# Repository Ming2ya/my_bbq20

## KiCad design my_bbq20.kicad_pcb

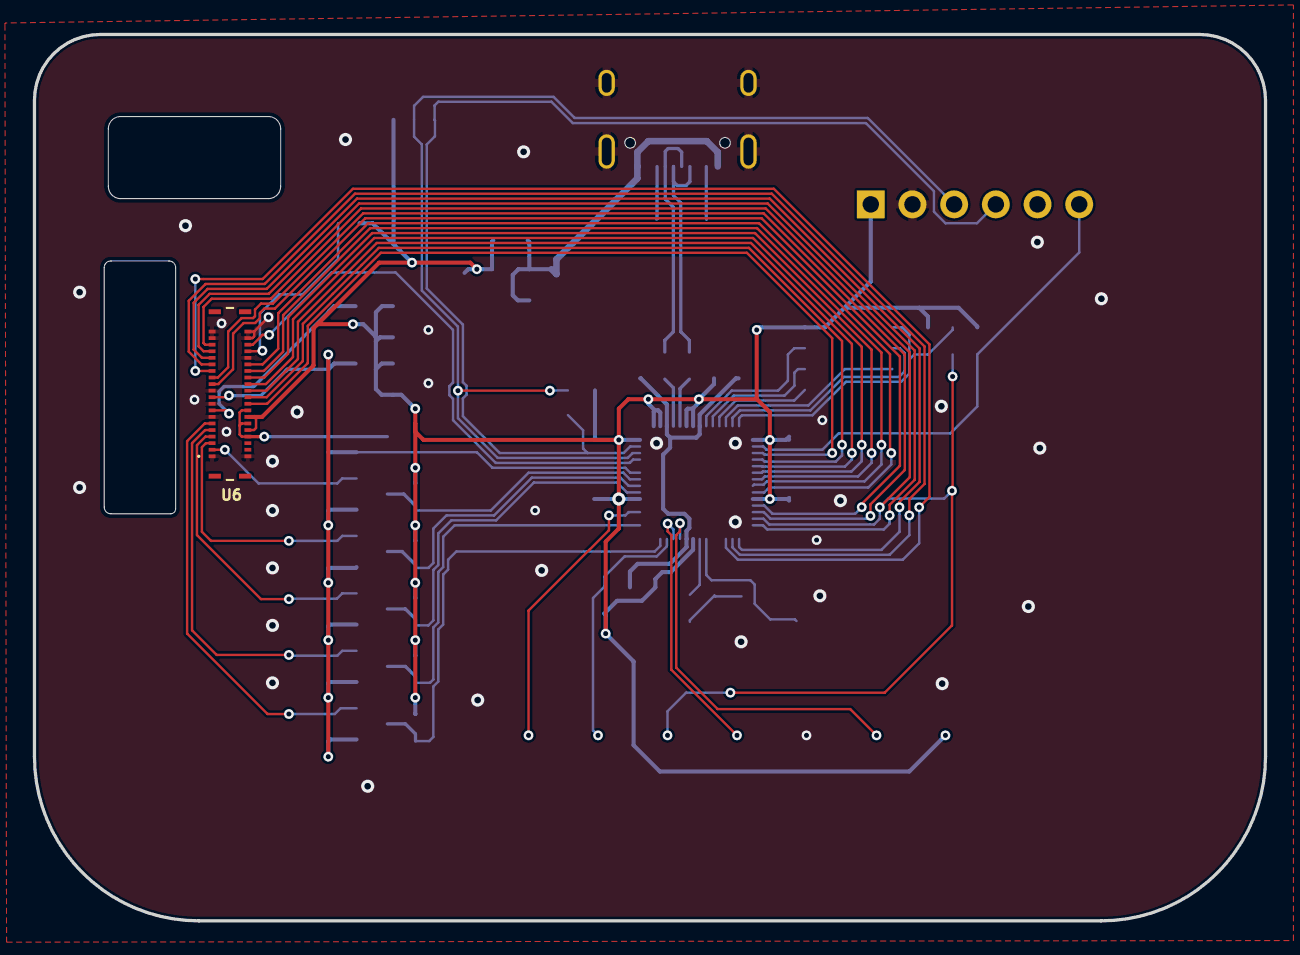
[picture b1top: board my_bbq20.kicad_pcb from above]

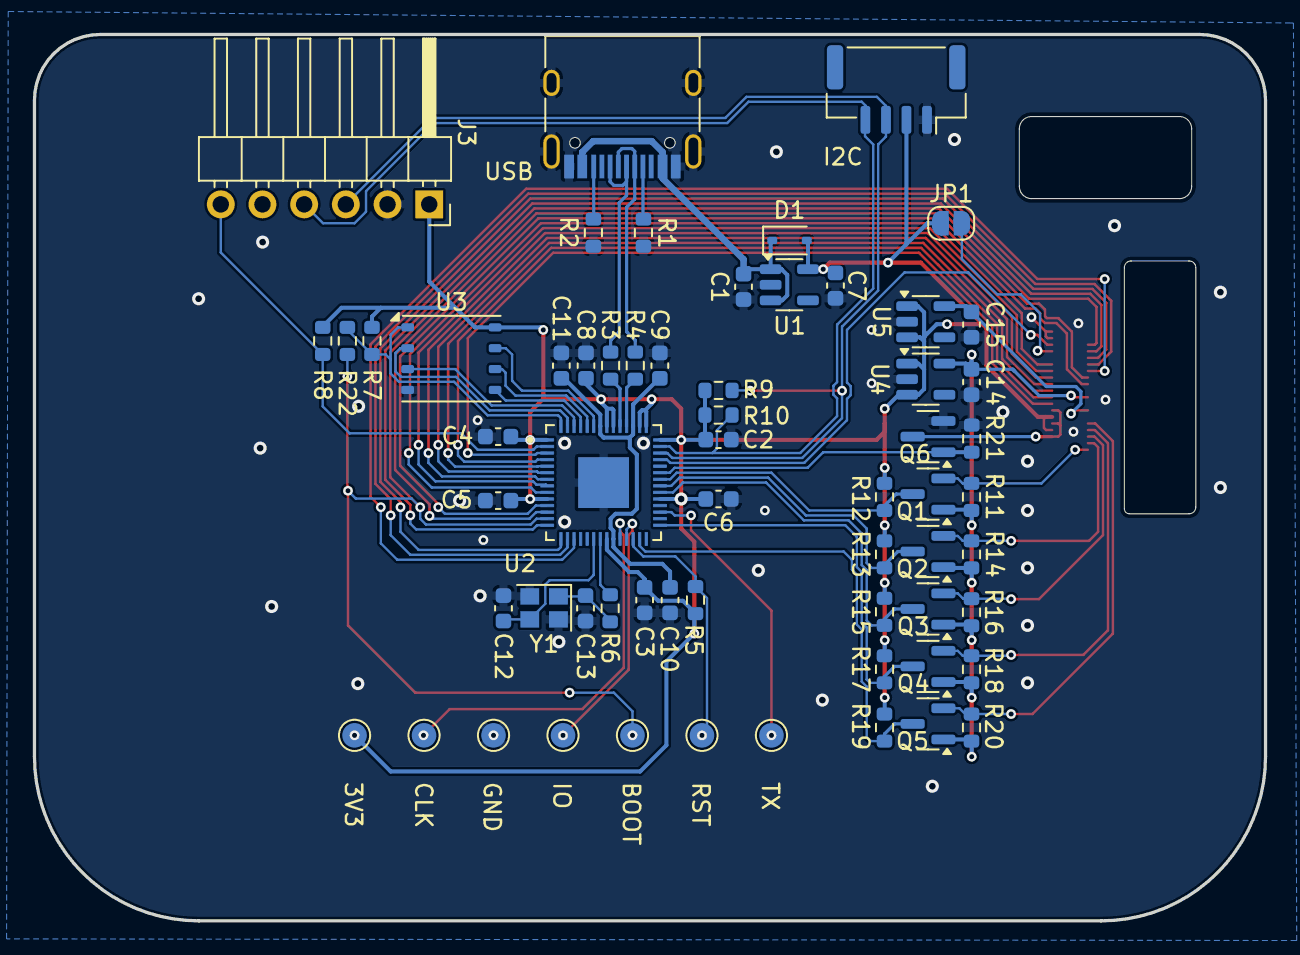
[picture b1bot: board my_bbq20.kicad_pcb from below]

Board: 2 copper layers, 75.0 x 54.0 mm, 62 parts (61 on the bottom side), 56 nets.

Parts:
3V3: TestPoint; TestPoint_Pad_D1.5mm
BOOT: TestPoint; TestPoint_Pad_D1.5mm
C1, C2: 10uF; C_0603_1608Metric
C3, C4, C5, C6, C7, C9, C10, C14, C15: 0.1uF; C_0603_1608Metric
C8, C11: 1uF; C_0603_1608Metric
C12, C13: 12pF; C_0603_1608Metric
CLK: TestPoint; TestPoint_Pad_D1.5mm
D1: D_Schottky_Small; D_SOD-323
GND: TestPoint; TestPoint_Pad_D1.5mm
I2C: Conn_01x04; JST_GH_SM04B-GHS-TB_1x04-1MP_P1.25mm_Horizontal
IO: TestPoint; TestPoint_Pad_D1.5mm
J3: PMOD; Pmod_PinHeader_1x06_P2.54mm_Horizontal
JP1: SolderJumper_2_Open; SolderJumper-2_P1.3mm_Open_RoundedPad1.0x1.5mm
Q1, Q2, Q3, Q4, Q5, Q6: BSS138; SOT-23
R1, R2: 5.1k; R_0603_1608Metric
R3, R4: 27R; R_0603_1608Metric
R5, R7, R11, R12, R13, R14, R15, R16, R17, R18, R19, R20, R21: 10k; R_0603_1608Metric
R6, R22: 1k; R_0603_1608Metric
R8, R9, R10: 4.7k; R_0603_1608Metric
RST: TestPoint; TestPoint_Pad_D1.5mm
TX: TestPoint; TestPoint_Pad_D1.5mm
U1: AP2112K-3.3; SOT-23-5
U2: QFN40P700X700X90-57N
U3: W25Q64JV; my_WSON-8-1EP_6x5mm_P1.27mm_EP3.4x4mm
U4: ME6212C18M5G; SOT-23-5
U5: ME6212C28M5G; SOT-23-5
U6: BBQ20KBD; HRS_BM20B_0.8_-40DS-0.4V_51_
USB: USB_C_Receptacle_USB2.0_16P; USB_C_Receptacle_HRO_TYPE-C-31-M-12
Y1: Crystal_GND24_Small; Crystal_SMD_2520-4Pin_2.5x2.0mm

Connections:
+1V8: C14.1, Q1.1 (G), Q2.1 (G), Q3.1 (G), Q4.1 (G), Q5.1 (G), R11.1, R14.1, R16.1, R18.1, R20.1, U4.5 (OUT), U6.10 (1V8)
+2V8: C15.1, U5.5 (OUT), U6.8 (2V8)
+3V3: 3V3.1, C2.1, C3.2, C4.2, C5.2, C6.2, C7.2, C8.2, D1.2 (A), I2C.2, J3.1, JP1.1 (A), R5.1, R7.1, R8.1, R9.1, R10.1, R12.1, R13.1, R15.1, R17.1, R19.1, U1.5 (VOUT), U2.1 (IOVDD), U2.10 (IOVDD), U2.22 (IOVDD), U2.33 (IOVDD), U2.42 (IOVDD), U2.43 (ADC_AVDD), U2.44 (VREG_IN), U2.48 (USB_VDD), U2.49 (IOVDD), U3.8 (VDD), U4.1 (IN), U4.3 (EN), U5.1 (IN), U5.3 (EN), U6.34 (LEDA), U6.36 (LEDA)
+5V: C1.1, D1.1 (K), U1.1 (VIN), U1.3 (EN), USB.A4 (VBUS), USB.A9 (VBUS), USB.B4 (VBUS), USB.B9 (VBUS)
/BACKLIGHT: Q6.1 (G), R21.1, U2.37 (GPIO25)
/BOOTSEL: BOOT.1, R22.1, U2.13 (GPIO10), U6.18 (COL7)
/COL1: U2.11 (GPIO8), U6.12 (COL1)
/COL2: U2.12 (GPIO9), U6.13 (COL2)
/COL3: U2.17 (GPIO14), U6.14 (COL3)
/COL4: U2.16 (GPIO13), U6.15 (COL4)
/COL5: U2.15 (GPIO12), U6.16 (COL5)
/COL6: U2.14 (GPIO11), U6.17 (COL6)
/INT: J3.6, R8.2, U2.2 (GPIO0)
/Keyborad/TP_MOTION_1V8: Q3.2 (S), R16.2, U6.4 (TP_MOTION)
/Keyborad/TP_RESET_1V8: Q5.2 (S), R20.2, U6.6 (TP_RESET)
/Keyborad/TP_SCL_1V8: Q2.2 (S), R14.2, U6.3 (TP_SCL)
/Keyborad/TP_SDA_1V8: Q4.2 (S), R18.2, U6.5 (TP_SDA)
/Keyborad/TP_SHUTDOWN_1V8: Q1.2 (S), R11.2, U6.2 (TP_SHUTDOWN)
/MIC: U2.39 (GPIO27_ADC1), U6.23 (MIC)
/QSPI_SCLK: U2.52 (QSPI_SCLK), U3.6 (SCK)
/QSPI_SD0: U2.53 (QSPI_SD0), U3.5 (DI/IO0)
/QSPI_SD1: U2.55 (QSPI_SD1), U3.2 (DO/IO1)
/QSPI_SD2: U2.54 (QSPI_SD2), U3.3 (~WP/IO2)
/QSPI_SD3: U2.51 (QSPI_SD3), U3.7 (~HOLD/IO3)
/ROW1: U2.3 (GPIO1), U6.32 (ROW1)
/ROW2: U2.4 (GPIO2), U6.31 (ROW2)
/ROW3: U2.5 (GPIO3), U6.30 (ROW3)
/ROW4: U2.6 (GPIO4), U6.29 (ROW4)
/ROW5: U2.7 (GPIO5), U6.28 (ROW5)
/ROW6: U2.8 (GPIO6), U6.27 (ROW6)
/ROW7: U2.9 (GPIO7), U6.26 (ROW7)
/SCL: I2C.4, J3.4, R10.2, U2.41 (GPIO29_ADC3)
/SDA: I2C.3, J3.3, R9.2, U2.40 (GPIO28_ADC2)
/SWCLK: CLK.1, U2.24 (SWCLK)
/SWDIO: IO.1, U2.25 (SWD)
/TP_MOTION: Q3.3 (D), R15.2, U2.34 (GPIO22)
/TP_RESET: Q5.3 (D), R19.2, U2.27 (GPIO16)
/TP_SCL: Q2.3 (D), R13.2, U2.35 (GPIO23)
/TP_SDA: Q4.3 (D), R17.2, U2.29 (GPIO18)
/TP_SHUTDOWN: Q1.3 (D), R12.2, U2.36 (GPIO24)
/TX: TX.1, U2.31 (GPIO20)
/USB_D+: R3.1, USB.A6 (D+), USB.B6 (D+)
/USB_D-: R4.1, USB.A7 (D-), USB.B7 (D-)
/~QSPI_CS: R7.2, R22.2, U2.56 (QSPI_SS), U3.1 (~CS)
/~RESET: R5.2, RST.1, U2.26 (RUN)
GND: C1.2, C2.2, C3.1, C4.1, C5.1, C6.1, C7.1, C8.1, C9.2, C10.2, C11.2, C12.1, C13.1, C14.2, C15.2, GND.1, I2C.1, J3.2, Q6.2 (S), R1.2, R2.2, R21.2, U1.2 (GND), U2.57 (GND), U3.4 (GND), U4.2 (GND), U5.2 (GND), U6.1 (GND), U6.7 (GND), U6.9 (GND), U6.11 (GND), U6.19 (GND), U6.20 (GND), U6.21 (GND), U6.22 (AGND), U6.25 (GND), U6.40 (GND), USB.A1 (GND), USB.A12 (GND), USB.B1 (GND), USB.B12 (GND), USB.S1 (SHIELD), Y1.2, Y1.4
unnamed: C13.2, R6.1, Y1.1
unnamed: R1.1, USB.A5 (CC1)
unnamed: R2.1, USB.B5 (CC2)
unnamed: JP1.2 (B), U6.24 (MIC_VDD)
unnamed: Q6.3 (D), U6.33 (LEDK), U6.35 (LEDK), U6.37 (LEDK)
unnamed: R3.2, U2.47 (USB_D+)
unnamed: R4.2, U2.46 (USB_D-)
unnamed: C9.1, C10.1, C11.1, U2.23 (DVDD), U2.45 (VREG_VOUT), U2.50 (DVDD)
unnamed: C12.2, U2.20 (XIN), Y1.3
unnamed: R6.2, U2.21 (XOUT)

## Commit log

2025-02-07 sch1
2025-02-09 footprint1
2025-02-10 PCB1
2025-02-10 PCB Lay
2025-02-11 PCB2
2025-02-15 pcb Cu
2025-02-16 PCB 3
2025-02-24 DRC1
2025-02-24 DRC2
